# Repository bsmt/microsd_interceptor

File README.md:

# microsd interceptor

It's a PCB that plugs into MicroSD sockets. It has its own MicroSD socket (DM3AT-SF-PEJM5) that's connected to the other end. All of the signals are also broken out to a 0.1" header. Pretty simple.

MicroSD cards are about 0.7mm thick, so you'll need to find a PCB fab that makes thin boards. OSH park's 2oz PCBs are 0.8mm thick, which is close enough in my experience. There is no copper or soldermask on the top layer in the MicroSD male section, so you can easily file or sand it down a little if you need to.

Oh, and there's a footprint with the MicroSD card outline and pads in the microsd.pretty library. Feel free to use that in your own projects. Nobody should have to experience the tedium of interpreting the physical dimension specs and drawing that in Kicad again.

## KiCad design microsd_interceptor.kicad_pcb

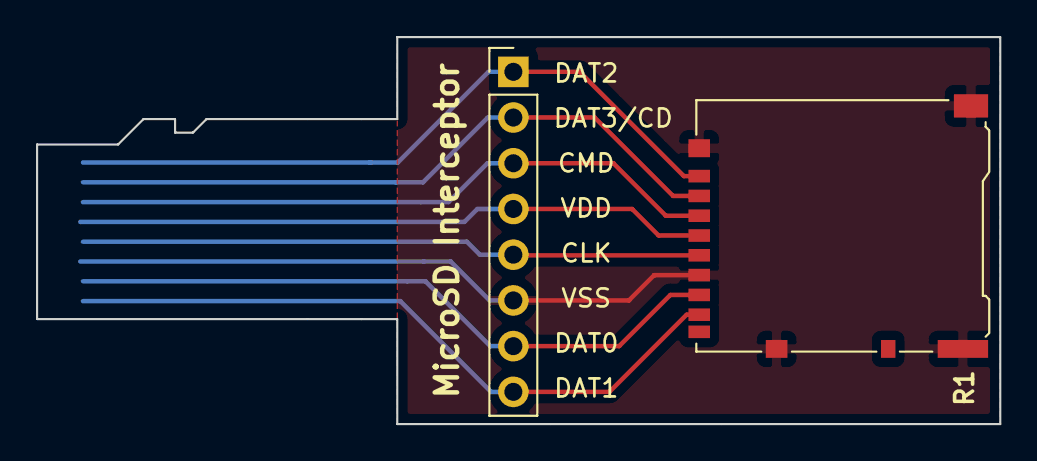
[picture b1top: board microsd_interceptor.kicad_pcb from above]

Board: 2 copper layers, 53.5 x 21.5 mm, 3 parts (0 on the bottom side), 8 nets.

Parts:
J1: Micro_SD_Card male; microsd_card
J2: Conn_01x08_Male; PinHeader_1x08_P2.54mm_Vertical
J3: Micro_SD_Card_Det_Hirose_DM3AT; microSD_HC_Hirose_DM3AT-SF-PEJM5

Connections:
GND: J1.6, J2.6, J3.6, J3.11
unnamed: J1.1, J2.1, J3.1
unnamed: J1.2, J2.2, J3.2
unnamed: J1.3, J2.3, J3.3
unnamed: J1.4, J2.4, J3.4
unnamed: J1.5, J2.5, J3.5
unnamed: J1.7, J2.7, J3.7
unnamed: J1.8, J2.8, J3.8

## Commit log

2020-09-19 init
2020-09-19 pick chore
